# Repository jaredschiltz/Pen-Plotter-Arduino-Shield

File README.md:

# Pen-Plotter-Arduino-Shield

## This is a Pen Plotter Arduino Shield to be used with an Uno R3 Arduino. Rev A

This shield is designed to work with an Arduino that has been loaded with GRBL 0.9. All electrical pin definitions are the default pin assignments specified in the 0.9 version of the code. N.B, servo PWM control uses PIN D11 (the Z-Limit signal). Pen-up command is M03 S255 and Pen-down command is M03 S0. With the current firmware, the angle delta between S255 and S0, is 90 degrees. A couple notes about this shield:

- This shield is a modification of the original CNC shield. There is no Z-axis motor control. An AGFRC A20CLS servo is being used to move the pen up and down. This high torque (7.5 kg-cm) servo runs on a voltage between 4.8 Volts and 8.4 Volts. To generate a 5.0 servo voltage, from the 12 V stepper motor power supply, a LM2596 buck switching regulator is used. The maximum 3 A output is enough to adequately drive the A20CLS motor. I was unable to find a maximum stall current specification for this particular servo, but the assumption is that it is a least an amp.
- The Y-axis is driven by two mirrored stepper motors, so this shield ties these control signals together on the board, rather than using a jumper. This saves some board space.
- Change glass fuse to PPTC resettable fuse. Fuse specs: 16 V, 8 A hold, 13.6 A trip
- Remove 10K pullup on enable signal. Each driver board has a built-in 20K pullup.
- Make limit switch connections 3 conductors, instead of 2 conductors. The OpenBuilds limit switches are a three wire interface.
- Remove jumper connections to EN, STEPS, DIRS. It is not necessary to expose these. Remove jumper connections to SPNEN, SPNDIR, COOLEN (these are unused by the pen plotter). Remove header to UART signals, SPI, and power connections. All of these removals will free up board space.
- Make mounting screw hole locations accessible.

The following changes should be made to Rev A:

- No changes need to be implemented to date

Parts list:
|Designator |Designation |MFG |MFG Part No. |Supplier|Supplier Part No. |Quantity|
|----------------------|------------------------------------------------------------------------------------------|---------------------------|-----------------------|--------|-------------------------------|--------|
|J3 |Vertical Connector Header, 2-Pos, 2.54 mm, 6 mm contact length |Wurth Elektronik |61300211121 |Digikey |732-5315-ND |1 |
|J4/J23,J22/J19,J20/J21|Vertical Connector Header, 2-Pos, 2.54 mm, 6 mm contact length |Wurth Elektronik |61300421121 |Digikey |732-5294-ND |3 |
|D1 |1N5824 5 A Schottky Diode |Vishay |SB520-E3/54 |Digikey |SB520-E3/54GICT-ND |1 |
|C2,C1,C3 |100uF 50 V |Panasonic |EEU-FM1H101B |Digikey |P19712CT-ND |3 |
|J6,J2,J1,J10,J7,J9 |8 Position Header Connector 0.100" (2.54mm) Through Hole |Sullins Connector Solutions|PPTC081LFBN-RC |Digikey |S7006-ND |6 |
|J5,J8,J11 |Vertical Connector Header, 4-Pos, 2.54 mm, 6 mm contact length |Wurth Elektronik |61300411121 |Digikey |732-5317-ND |3 |
|U1 |IC REG BUCK LM2596 5V 3A TO263-5 |UMW |LM2596S-5.0 |Digikey |4518-LM2596S-5.0CT-ND |1 |
|C5,C4 |330 uF, 50V, Low-ESR 58 m-ohm |Kemet |ESW337M050AH4EA |Digikey |399-6661-1-ND |2 |
|L1 |33 uH, 3.6 A, 51 m-Ohm |Abracon LLC |AIUR-06-330K |Digikey |AIUR-06-330K-ND |1 |
|J13 |2 Position Wire to Board Terminal Block Horizontal with Board 0.197" (5.00mm) Through Hole|Wurth Elektronik |691137710002 |Digikey |732-10955-ND |1 |
|J14,J15,J16,J12,J17 |Vertical Connector Header, 3-Pos, 2.54 mm, 6 mm contact length |Wurth Elektronik |61300311121 |Digikey |732-5316-ND |5 |
|J18 |Vertical Connector Header, (2 Rows / 6-Pos), 2.54 mm, 6 mm contact length |Wurth Elektronik |61300621121 |Digikey |732-5295-ND |1 |
|U3 |Vertical Connector Header, 6-Pos, 2.54 mm, 6 mm contact length |Wurth Elektronik |61300611121 |Digikey |732-5319-ND |1 |
|U2, U7 |Vertical Connector Header, 8-Pos, 2.54 mm, 6 mm contact length |Wurth Elektronik |61300811121 |Digikey |732-5321-ND |1 |
|U6 |Vertical Connector Header, 10-Pos, 2.54 mm, 6 mm contact length |Wurth Elektronik |61301011121 |Digikey |732-2670-ND | |
|F1 |PPTC Radial Resettable Fuse (8.0 A Hold Current, 13.5 A Trip Current, 16 V Max) |RFE/Fuzetec |FRG800-16F |Digikey |3451-FRG800-16F-ND |1 |
|S1 |MOMENTARY-SWITCH-SPST-PTH-6.0MM |CUI Devices |TS02-66-60-BK-160-LCR-D|Digikey |2223-TS02-66-60-BK-160-LCR-D-ND|1 |
|H3 |M3 Mounting Hole | | | | |1 |

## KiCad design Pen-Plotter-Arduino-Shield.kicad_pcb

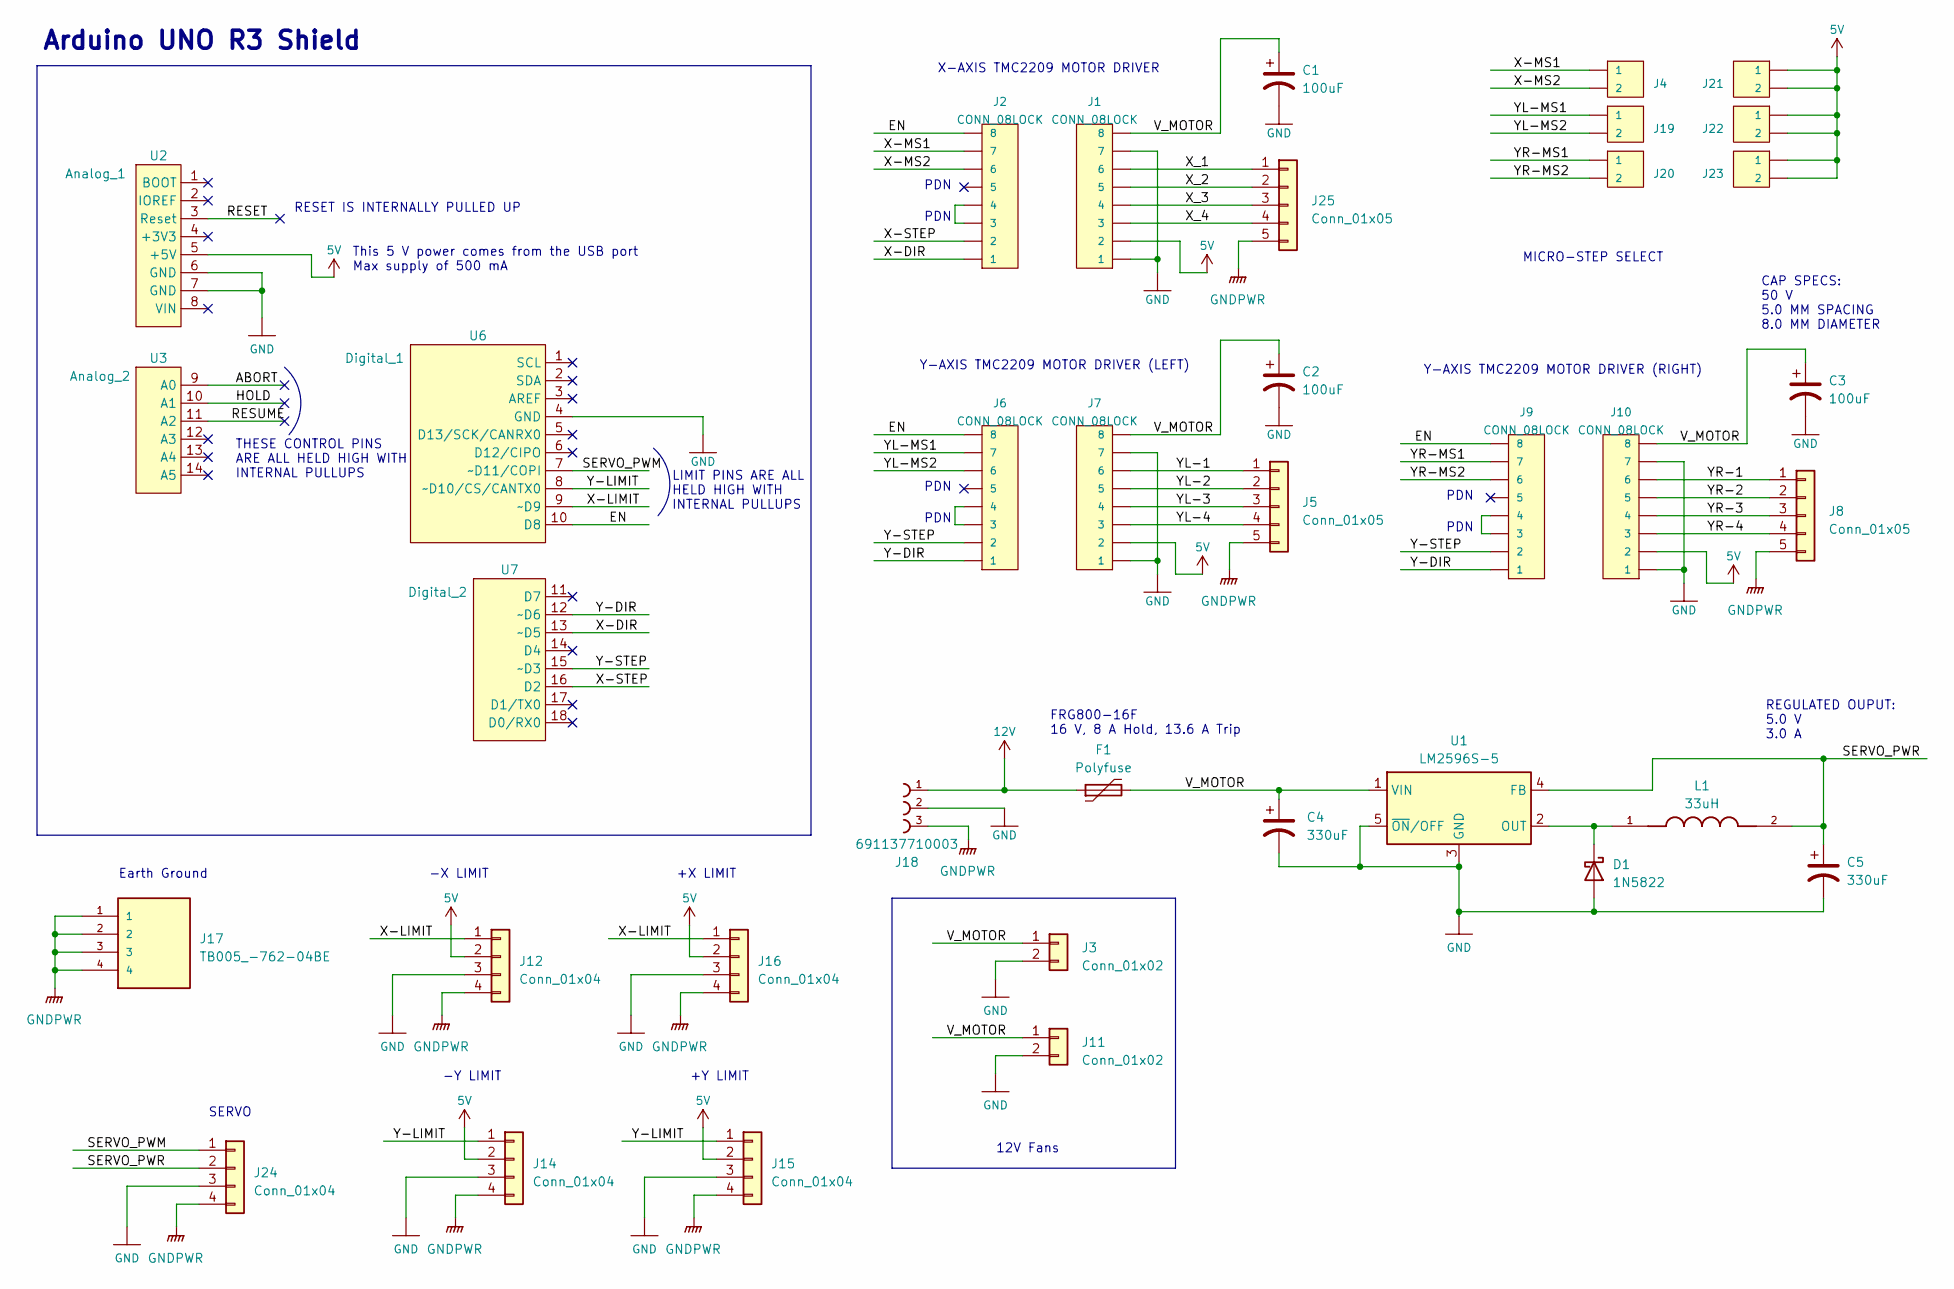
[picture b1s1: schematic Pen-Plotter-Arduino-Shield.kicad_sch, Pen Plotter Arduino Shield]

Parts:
C1, C2, C3: 100uF; CPOL-RADIAL-5MM-10MM
C4, C5: 330uF; CPOL-RADIAL-5MM-10MM
D1: 1N5822; D_DO-201AD_P15.24mm_Horizontal
F1: Polyfuse; FRG800-16F
J1, J2, J6, J7, J9, J10: CONN_08LOCK; 1X08_LOCK
J3, J11: Conn_01x02; JST_XH_B2B-XH-A_1x02_P2.50mm_Vertical
J4, J19, J20, J21, J22, J23: CONN_02LOCK; 1X02_LOCK
J5, J8, J25: Conn_01x05; JST_XH_B5B-XH-A_1x05_P2.50mm_Vertical
J12, J14, J15, J16, J24: Conn_01x04; JST_XH_B4B-XH-A_1x04_P2.50mm_Vertical
J17: TB005_-762-04BE; CUI_TB005 -762-04BE; DigiKey_Part_Number TB005-762-04BE-ND
J18: 691137710003
L1: 33uH; INDRD750W80D1350H1800; PARTREV 6/23/2022
U1: LM2596S-5; TO-263-5_TabPin3
U2: Analog_1; Arduino_PinSocket_1x08_P2.54mm_Vertical
U3: Analog_2; Arduino_PinSocket_1x06_P2.54mm_Vertical
U6: Digital_1; Arduino_PinSocket_1x10_P2.54mm_Vertical
U7: Digital_2; Arduino_PinSocket_1x08_P2.54mm_Vertical

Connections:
5V: J1.2, J7.2, J10.2, J12.2, J14.2, J15.2, J16.2, J21.1, J21.2, J22.1, J22.2, J23.1, J23.2, U2.5 (+5V)
12V: F1.1, J18.1
/ABORT: U3.9 (A0)
/EN: J2.8, J6.8, J9.8, U6.10 (D8)
/HOLD: U3.10 (A1)
/RESET: U2.3 (Reset)
/RESUME: U3.11 (A2)
/SERVO_PWM: J24.1, U6.7 (~D11/COPI)
/SERVO_PWR: C5.1, J24.2, L1.2, U1.4 (FB)
/V_MOTOR: C1.1, C2.1, C3.1, C4.1, F1.2, J1.8, J3.1, J7.8, J10.8, J11.1, U1.1 (VIN)
/X-DIR: J2.1, U7.13 (~D5)
/X-LIMIT: J12.1, J16.1, U6.9 (~D9)
/X-MS1: J2.7, J4.1
/X-MS2: J2.6, J4.2
/X-STEP: J2.2, U7.16 (D2)
/X_1: J1.6, J25.1
/X_2: J1.5, J25.2
/X_3: J1.4, J25.3
/X_4: J1.3, J25.4
/Y-DIR: J6.1, J9.1, U7.12 (~D6)
/Y-LIMIT: J14.1, J15.1, U6.8 (~D10/CS/CANTX0)
/Y-STEP: J6.2, J9.2, U7.15 (~D3)
/YL-1: J5.1, J7.6
/YL-2: J5.2, J7.5
/YL-3: J5.3, J7.4
/YL-4: J5.4, J7.3
/YL-MS1: J6.7, J19.1
/YL-MS2: J6.6, J19.2
/YR-1: J8.1, J10.6
/YR-2: J8.2, J10.5
/YR-3: J8.3, J10.4
/YR-4: J8.4, J10.3
/YR-MS1: J9.7, J20.1
/YR-MS2: J9.6, J20.2
GND: C1.2, C2.2, C3.2, C4.2, C5.2, D1.2 (A), J1.1, J1.7, J3.2, J7.1, J7.7, J10.1, J10.7, J11.2, J12.3, J14.3, J15.3, J16.3, J18.2, J24.3, U1.3 (GND), U1.5 (~ON/OFF), U2.6 (GND), U2.7 (GND), U6.4 (GND)
GNDPWR: J5.5, J8.5, J12.4, J14.4, J15.4, J16.4, J17.1, J17.2, J17.3, J17.4, J18.3, J24.4, J25.5
unnamed: D1.1 (K), L1.1, U1.2 (OUT)
unnamed: J2.3, J2.4
unnamed: J6.3, J6.4
unnamed: J9.3, J9.4

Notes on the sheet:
THESE CONTROL PINS ARE ALL HELD HIGH WITH INTERNAL PULLUPS
RESET IS INTERNALLY PULLED UP
+X LIMIT
Y-AXIS TMC2209 MOTOR DRIVER (RIGHT)
FRG800-16F 16 V, 8 A Hold, 13.6 A Trip
-X LIMIT
X-AXIS TMC2209 MOTOR DRIVER
Arduino UNO R3 Shield
REGULATED OUPUT: 5.0 V 3.0 A
This 5 V power comes from the USB port Max supply of 500 mA
+Y LIMIT
12V Fans
PDN
CAP SPECS: 50 V 5.0 MM SPACING 8.0 MM DIAMETER
Earth Ground
MICRO-STEP SELECT
Y-AXIS TMC2209 MOTOR DRIVER (LEFT)
SERVO
-Y LIMIT
LIMIT PINS ARE ALL HELD HIGH WITH INTERNAL PULLUPS

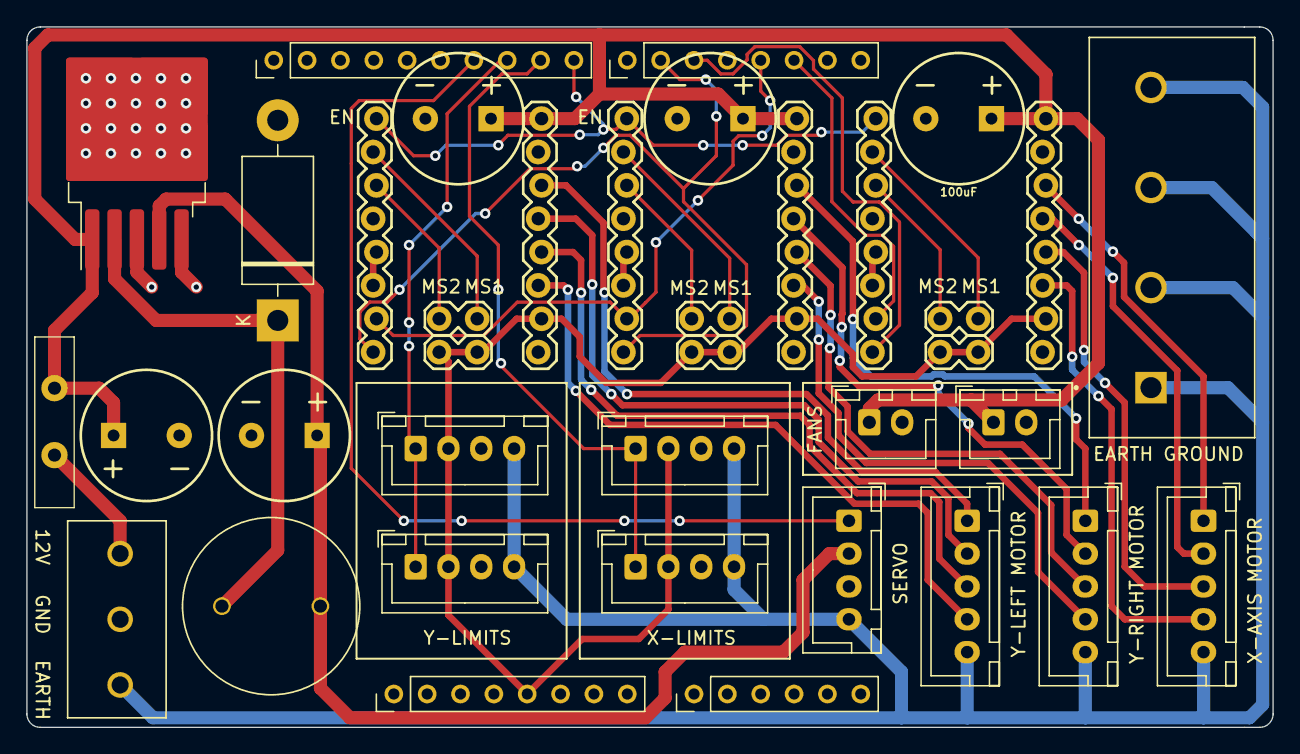
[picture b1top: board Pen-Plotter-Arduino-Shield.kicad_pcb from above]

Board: 2 copper layers, 94.9 x 53.3 mm, 37 parts (0 on the bottom side), 36 nets.

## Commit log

2024-03-21 add source for rev-
2024-04-10 Add Rev A notes
2024-07-30 update all files to Revision A
